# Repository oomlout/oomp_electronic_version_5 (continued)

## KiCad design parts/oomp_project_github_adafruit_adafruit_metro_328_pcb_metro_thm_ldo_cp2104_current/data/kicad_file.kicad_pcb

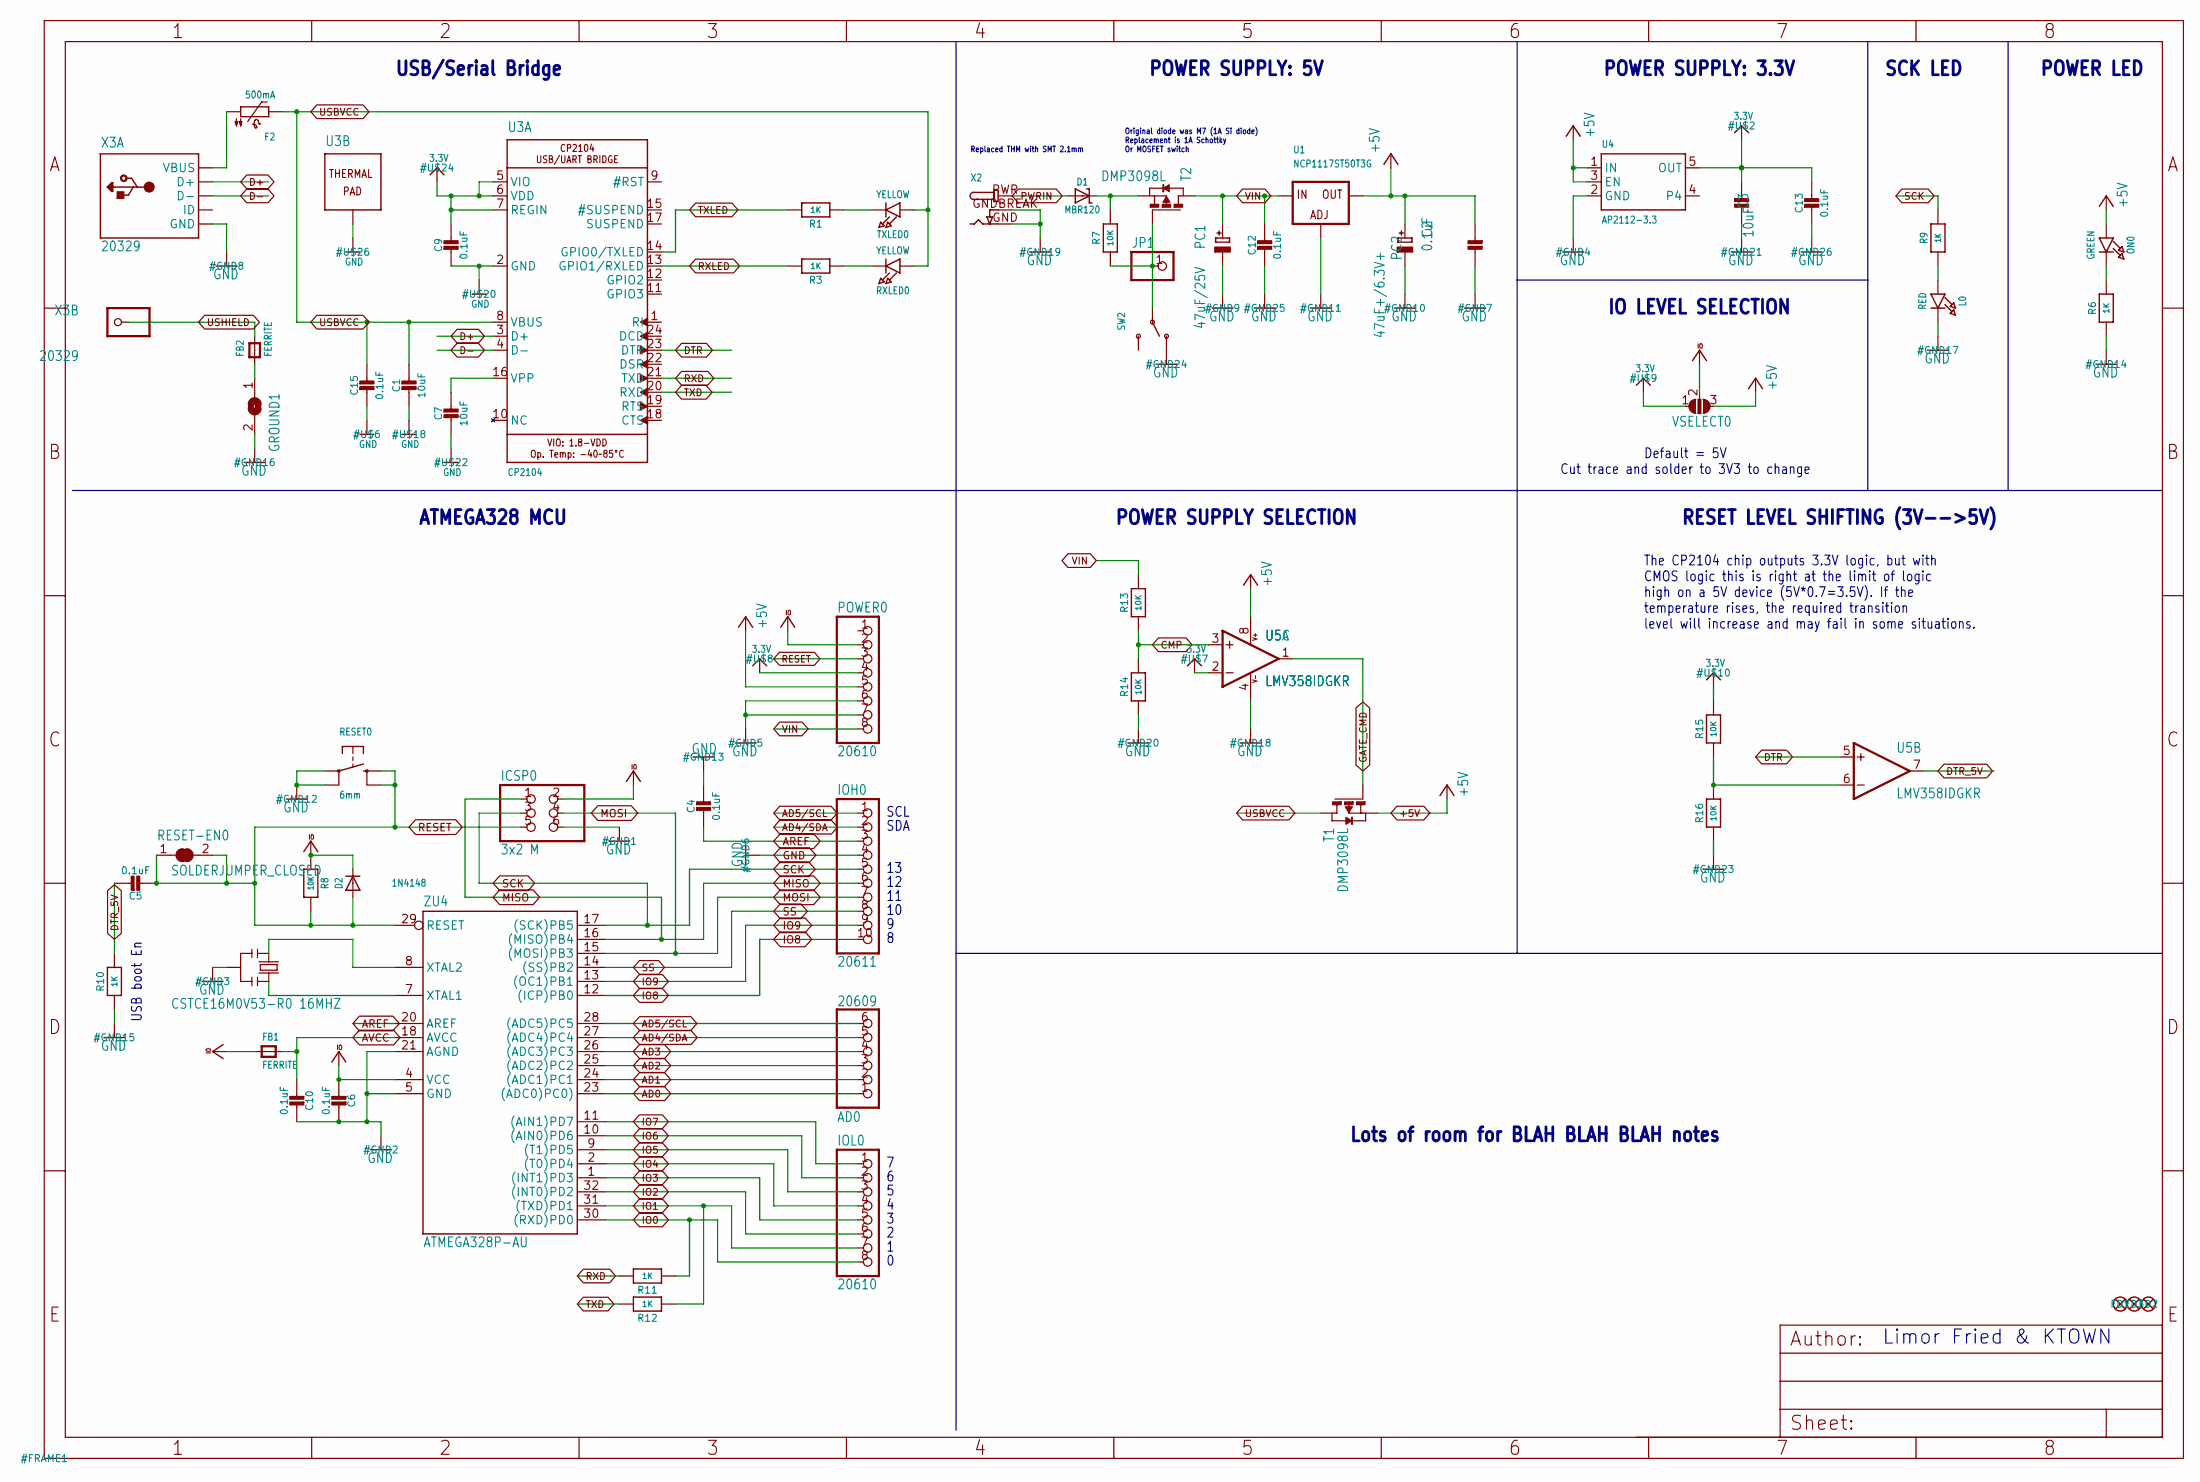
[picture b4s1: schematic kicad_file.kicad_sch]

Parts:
AD0: 20609; 1X06_OVAL
C1, C3, C7: 10uF; 0805-NO
C2, C4, C5, C6, C9, C12, C13, C15: 0.1uF; 0805-NO
C10: 0.1uF; 0805_10MGAP
D1: MBR120; SOD-123
D2: 1N4148; SOD-323
F2: 500mA; 1206-NO
FB1, FB2: FERRITE; 0805-NO
FD1, FD2, FD3: FIDUCIAL_1MM
GROUND1: SJ
ICSP0: 3x2 M; 2X03_ROUND_70MIL
IOH0: 20611; 1X10_OVAL
IOL0: 20610; 1X08_OVAL
JP1: HEADER-1X1ROUND; 1X01_ROUND
L0: RED; CHIPLED_0805_NOOUTLINE
ON0: GREEN; CHIPLED_0805_NOOUTLINE
PC1: 47uF/25V; PANASONIC_D
PC2: 47uF+/6.3V+; PANASONIC_D
POWER0: 20610; 1X08_OVAL
R1, R3, R6, R9, R10, R11, R12: 1K; 0805-NO
R7, R13, R14, R15, R16: 10K; 0805-NO
R8: 10K; _0805MP
RESET0: 6mm; EVQ-Q2
RESET-EN0: SOLDERJUMPER_CLOSED; SOLDERJUMPER_CLOSEDWIRE
RXLED0: YELLOW; CHIPLED_0805_NOOUTLINE
SW2: SWITCH_SPDT; SPDT_SMT_SSSS811101
T1, T2: DMP3098L; SOT-23
TXLED0: YELLOW; CHIPLED_0805_NOOUTLINE
U1: NCP1117ST50T3G; SOT223-R
U3: CP2104; QFN24_4MM_SMSC
U4: AP2112-3.3; SOT23-5
U5: LMV358IDGKR; MSOP08
VSELECT0: SOLDERJUMPER_2WAY; SOLDERJUMPER_2WAY_OPEN_NOPASTE
X2: DCBARRELPTH; DCJACK_2MM_PTH
X3: 20329; 4UCONN_20329_V2
Y2: CSTCE16M0V53-R0 16MHZ; RESONATOR
ZU4: ATMEGA328P-AU; TQFP32-08

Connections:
3.3V: C3.2, C9.1, C13.1, POWER0.4, R15.2, U3.5 (VIO), U3.6 (VDD), U3.7 (REGIN), U4.5 (OUT), U5.2 (-IN), VSELECT0.1
+5V: C2.2, ON0.A, PC2.+, POWER0.5, T1.2 (S), U1.2 (OUT), U1.4 (OUT), U4.1 (IN), U4.3 (EN), U5.8 (V+), VSELECT0.3
AD0: AD0.1, ZU4.23 ((ADC0)PC0))
AD1: AD0.2, ZU4.24 ((ADC1)PC1)
AD2: AD0.3, ZU4.25 ((ADC2)PC2)
AD3: AD0.4, ZU4.26 ((ADC3)PC3)
AD4/SDA: AD0.5, IOH0.2, ZU4.27 ((ADC4)PC4)
AD5/SCL: AD0.6, IOH0.1, ZU4.28 ((ADC5)PC5)
AREF: C4.2, IOH0.3, ZU4.20 (AREF)
AVCC: C10.2, FB1.2, ZU4.18 (AVCC)
CMP: R13.1, R14.2, U5.3 (+IN)
D+: U3.3 (D+), X3.D+
D-: U3.4 (D-), X3.D-
DTR: U3.23 (DTR), U5.5 (+IN)
DTR_5V: C5.1, R10.2, U5.7 (OUT)
GATE_CMD: T1.3 (G), U5.1 (OUT)
GND: C1.2, C2.1, C3.1, C4.1, C6.1, C7.2, C9.2, C10.1, C12.2, C13.2, C15.2, GROUND1.2, ICSP0.6, IOH0.4, L0.C, PC1.-, PC2.-, POWER0.6, POWER0.7, R6.1, R10.1, R14.1, R16.1, RESET0.A, RESET0.A' (P1), SW2.A (O), U1.1 (ADJ), U3.2 (GND), U3.THERM (TP), U4.2 (GND), U5.4 (V-), X2.GND, X2.GNDBREAK, X3.GND, Y2.2, ZU4.5 (GND), ZU4.21 (AGND)
IO0: IOL0.8, R11.1, ZU4.30 ((RXD)PD0)
IO1: IOL0.7, R12.1, ZU4.31 ((TXD)PD1)
IO2: IOL0.6, ZU4.32 ((INT0)PD2)
IO3: IOL0.5, ZU4.1 ((INT1)PD3)
IO4: IOL0.4, ZU4.2 ((T0)PD4)
IO5: IOL0.3, ZU4.9 ((T1)PD5)
IO6: IOL0.2, ZU4.10 ((AIN0)PD6)
IO7: IOL0.1, ZU4.11 ((AIN1)PD7)
IO8: IOH0.10, ZU4.12 ((ICP)PB0)
IO9: IOH0.9, ZU4.13 ((OC1)PB1)
MISO: ICSP0.1, IOH0.6, ZU4.16 ((MISO)PB4)
MOSI: ICSP0.4, IOH0.7, ZU4.15 ((MOSI)PB3)
unnamed: L0.A, R9.1
unnamed: FB2.1, GROUND1.1
unnamed: ON0.C, R6.2
unnamed: R3.1, RXLED0.C
unnamed: R1.1, TXLED0.C
unnamed: R15.1, R16.2, U5.6 (-IN)
unnamed: JP1.1, R7.1, SW2.B, T2.3 (G)
unnamed: D1.C, R7.2, T2.2 (S)
unnamed: C7.1, U3.16 (VPP)
PWRIN: D1.A, X2.PWR
RESET: C5.2, D2.A, ICSP0.5, POWER0.3, R8.1, RESET0.B (S), RESET0.B' (S1), RESET-EN0.1, RESET-EN0.2, ZU4.29 (RESET)
RXD: R11.2, U3.21 (TXD)
RXLED: R3.2, U3.13 (GPIO1/RXLED)
SCK: ICSP0.3, IOH0.5, R9.2, ZU4.17 ((SCK)PB5)
SS: IOH0.8, ZU4.14 ((SS)PB2)
TXD: R12.2, U3.20 (RXD)
TXLED: R1.2, U3.14 (GPIO0/TXLED)
USBVCC: C1.1, C15.1, F2.2, RXLED0.A, T1.1 (D), TXLED0.A, U3.8 (VBUS)
USHIELD: FB2.2, X3.BASE@1 (1), X3.BASE@2 (1), X3.SPRT@1 (1), X3.SPRT@2 (1), X3.SPRT@3 (1), X3.SPRT@4 (1)
VBUS: F2.1, X3.VBUS
VCCIO: C6.2, D2.C, FB1.1, ICSP0.2, POWER0.2, R8.2, VSELECT0.2, ZU4.4 (VCC)
VIN: C12.1, PC1.+, POWER0.8, R13.2, T2.1 (D), U1.3 (IN)
XTAL1: Y2.3, ZU4.7 (XTAL1)
XTAL2: Y2.1, ZU4.8 (XTAL2)

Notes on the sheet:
POWER LED
POWER SUPPLY: 5V
Lots of room for BLAH BLAH BLAH notes
RESET LEVEL SHIFTING (3V-->5V)
The CP2104 chip outputs 3.3V logic, but with CMOS logic this is right at the limit of logic high on a 5V device (5V*0.7=3.5V). If the temperature rises, the required transition level will increase and may fail in some situations.
Limor Fried & KTOWN
IO LEVEL SELECTION
SDA
POWER SUPPLY SELECTION
SCL
USB/Serial Bridge
Original diode was M7 (1A Si diode) Replacement is 1A Schottky Or MOSFET switch
ATMEGA328 MCU
SCK LED
Replaced THM with SMT 2.1mm
POWER SUPPLY: 3.3V
USB boot En
Default = 5V Cut trace and solder to 3V3 to change

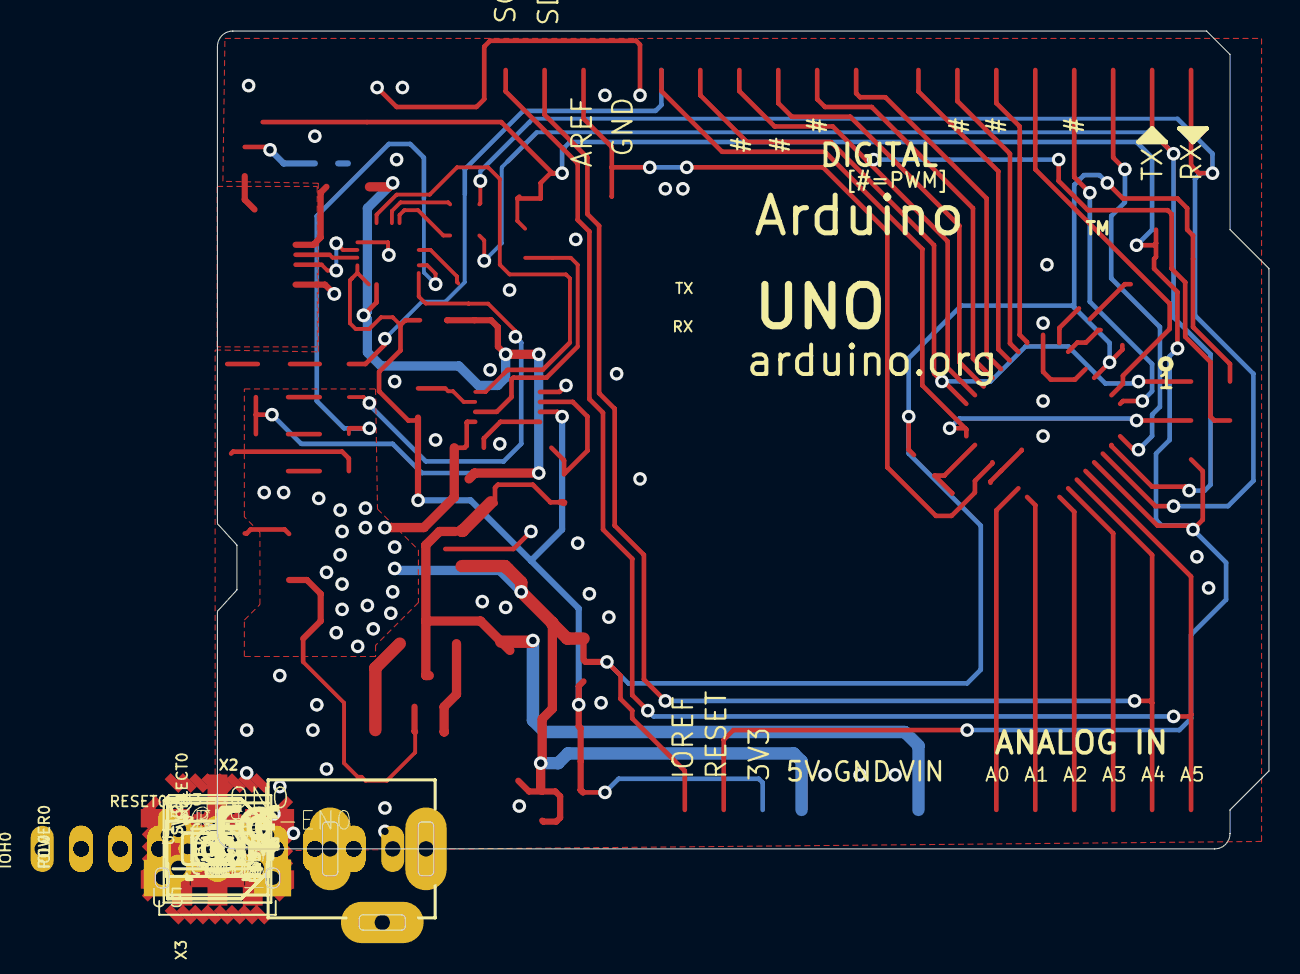
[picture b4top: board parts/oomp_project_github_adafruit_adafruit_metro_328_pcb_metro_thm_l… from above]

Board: 2 copper layers, 72.6 x 58.6 mm, 69 parts (1 on the bottom side), 53 nets.

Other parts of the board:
U$4: METROSILK_CP2104_TOP
U$14: METROSILK_BOT
U$15: PCBFEAT-REV-040
U$16: SYMBOL_FCC_TINY
U$17: SYMBOL_CE_TINY
UNK_HOLE_0: dummyfp0
UNK_HOLE_1: dummyfp1
UNK_HOLE_2: dummyfp2
UNK_HOLE_3: dummyfp3

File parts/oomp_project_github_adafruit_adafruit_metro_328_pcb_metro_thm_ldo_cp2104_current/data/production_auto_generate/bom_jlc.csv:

Comment,Designator,Footprint,LCSC Part #
,JP1,Metro THM+LDO Rev C - CP2104-import-fps:1X01_ROUND,C7501259
,X2,Metro THM+LDO Rev C - CP2104-import-fps:DCJACK_2MM_PTH,
,U$14,Metro THM+LDO Rev C - CP2104-import-fps:METROSILK_BOT,
,U$4,Metro THM+LDO Rev C - CP2104-import-fps:METROSILK_CP2104_TOP,
,U$15,Metro THM+LDO Rev C - CP2104-import-fps:PCBFEAT-REV-040,
,GROUND1,Metro THM+LDO Rev C - CP2104-import-fps:SJ,
,VSELECT0,Metro THM+LDO Rev C - CP2104-import-fps:SOLDERJUMPER_2WAY_OPEN_NOPASTE,
,RESET-EN0,Metro THM+LDO Rev C - CP2104-import-fps:SOLDERJUMPER_CLOSEDWIRE,
,SW2,Metro THM+LDO Rev C - CP2104-import-fps:SPDT_SMT_SSSS811101,
,U$17,Metro THM+LDO Rev C - CP2104-import-fps:SYMBOL_CE_TINY,
,U$16,Metro THM+LDO Rev C - CP2104-import-fps:SYMBOL_FCC_TINY,
0.1uF,"C2,C4,C5,C6,C9,C12,C13,C15",Metro THM+LDO Rev C - CP2104-import-fps:0805-NO,
0.1uF,C10,Metro THM+LDO Rev C - CP2104-import-fps:0805_10MGAP,
10K,"R7,R13,R14,R15,R16",Metro THM+LDO Rev C - CP2104-import-fps:0805-NO,C17414
10K,R8,Metro THM+LDO Rev C - CP2104-import-fps:_0805MP,C17414
10uF,"C1,C3,C7",Metro THM+LDO Rev C - CP2104-import-fps:0805-NO,
1K,"R1,R3,R6,R9,R10,R11,R12",Metro THM+LDO Rev C - CP2104-import-fps:0805-NO,C17513
1N4148,D2,Metro THM+LDO Rev C - CP2104-import-fps:SOD-323,
20329,X3,Metro THM+LDO Rev C - CP2104-import-fps:4UCONN_20329_V2,
20609,AD0,Metro THM+LDO Rev C - CP2104-import-fps:1X06_OVAL,C37208
20610,"IOL0,POWER0",Metro THM+LDO Rev C - CP2104-import-fps:1X08_OVAL,C492421
20611,IOH0,Metro THM+LDO Rev C - CP2104-import-fps:1X10_OVAL,C57369
3x2 M,ICSP0,Metro THM+LDO Rev C - CP2104-import-fps:2X03_ROUND_70MIL,
47uF+/6.3V+,PC2,Metro THM+LDO Rev C - CP2104-import-fps:PANASONIC_D,
47uF/25V,PC1,Metro THM+LDO Rev C - CP2104-import-fps:PANASONIC_D,
500mA,F2,Metro THM+LDO Rev C - CP2104-import-fps:1206-NO,
6mm,RESET0,Metro THM+LDO Rev C - CP2104-import-fps:EVQ-Q2,
AP2112-3.3,U4,Metro THM+LDO Rev C - CP2104-import-fps:SOT23-5,
ATMEGA328P-AU,ZU4,Metro THM+LDO Rev C - CP2104-import-fps:TQFP32-08,
CP2104,U3,Metro THM+LDO Rev C - CP2104-import-fps:QFN24_4MM_SMSC,
CSTCE16M0V53-R0 16MHZ,Y2,Metro THM+LDO Rev C - CP2104-import-fps:RESONATOR,
DMP3098L,"T1,T2",Metro THM+LDO Rev C - CP2104-import-fps:SOT-23,
FERRITE,"FB1,FB2",Metro THM+LDO Rev C - CP2104-import-fps:0805-NO,
FIDUCIAL_1MM,"FD1,FD2,FD3",Metro THM+LDO Rev C - CP2104-import-fps:FIDUCIAL_1MM,
GREEN,ON0,Metro THM+LDO Rev C - CP2104-import-fps:CHIPLED_0805_NOOUTLINE,
LMV358IDGKR,U5,Metro THM+LDO Rev C - CP2104-import-fps:MSOP08,
MBR120,D1,Metro THM+LDO Rev C - CP2104-import-fps:SOD-123,
NCP1117ST50T3G,U1,Metro THM+LDO Rev C - CP2104-import-fps:SOT223-R,
RED,L0,Metro THM+LDO Rev C - CP2104-import-fps:CHIPLED_0805_NOOUTLINE,
YELLOW,"RXLED0,TXLED0",Metro THM+LDO Rev C - CP2104-import-fps:CHIPLED_0805_NOOUTLINE,

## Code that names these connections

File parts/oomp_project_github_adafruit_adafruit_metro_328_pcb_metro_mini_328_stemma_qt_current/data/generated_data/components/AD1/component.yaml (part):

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      connected_to:
      - reference: U2
        pin_number: '10'
        pin_name: (ICP)PB0
    - number: '2'
      name: '2'
      electrical_type: passive
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      connected_to:
      - reference: U2
        pin_number: '11'
        pin_name: (OC1)PB1
    - number: '3'
      name: '3'
      electrical_type: passive
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      connected_to:
      - reference: U2
        pin_number: '12'
        pin_name: (SS)PB2
    - number: '4'
      name: '4'
      electrical_type: passive
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      connected_to:
      - reference: U2
        pin_number: '13'
        pin_name: (MOSI)PB3
    - number: '5'
      name: '5'
      electrical_type: passive
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      connected_to:
      - reference: U2
        pin_number: '14'
        pin_name: (MISO)PB4
    - number: '6'
      name: '6'
      electrical_type: passive
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        pin_name: A
      - reference: U2
        pin_number: '15'
        pin_name: (SCK)PB5
    size:
      local_graphics:
        measurement: symbol graphics only; excludes pins, properties, and text
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    pin_name: A
  - reference: U2
    pin_number: '10'
    pin_name: (ICP)PB0
  - reference: U2
    pin_number: '11'
    pin_name: (OC1)PB1
  - reference: U2
    pin_number: '12'
    pin_name: (SS)PB2
  - reference: U2
    pin_number: '13'
    pin_name: (MOSI)PB3
  - reference: U2
    pin_number: '14'
    pin_name: (MISO)PB4
  - reference: U2
    pin_number: '15'
    pin_name: (SCK)PB5
pcb:
  reference: AD1
  value: '20609'
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
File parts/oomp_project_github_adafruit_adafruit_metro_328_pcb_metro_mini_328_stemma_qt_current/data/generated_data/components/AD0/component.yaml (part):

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      connected_to:
      - reference: U2
        pin_number: '19'
        pin_name: (ADC0)PC0
    - number: '2'
      name: '2'
      electrical_type: passive
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      connected_to:
      - reference: U2
        pin_number: '20'
        pin_name: (ADC1)PC1
    - number: '3'
      name: '3'
      electrical_type: passive
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      connected_to:
      - reference: U2
        pin_number: '21'
        pin_name: (ADC2)PC2
    - number: '4'
      name: '4'
      electrical_type: passive
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      connected_to:
      - reference: U2
        pin_number: '22'
        pin_name: (ADC3)PC3
    - number: '5'
      name: '5'
      electrical_type: passive
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        pin_name: SDA
      - reference: U2
        pin_number: '23'
        pin_name: (ADC4)PC4
    - number: '6'
      name: '6'
      electrical_type: passive
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        pin_name: SCL
      - reference: U2
        pin_number: '24'
        pin_name: (ADC5)PC5
    size:
      local_graphics:
        measurement: symbol graphics only; excludes pins, properties, and text
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    pin_name: SCL
  - reference: U2
    pin_number: '19'
    pin_name: (ADC0)PC0
  - reference: U2
    pin_number: '20'
    pin_name: (ADC1)PC1
  - reference: U2
    pin_number: '21'
    pin_name: (ADC2)PC2
  - reference: U2
    pin_number: '22'
    pin_name: (ADC3)PC3
  - reference: U2
    pin_number: '23'
    pin_name: (ADC4)PC4
  - reference: U2
    pin_number: '24'
    pin_name: (ADC5)PC5
pcb:
  reference: AD0
  value: '20609'
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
